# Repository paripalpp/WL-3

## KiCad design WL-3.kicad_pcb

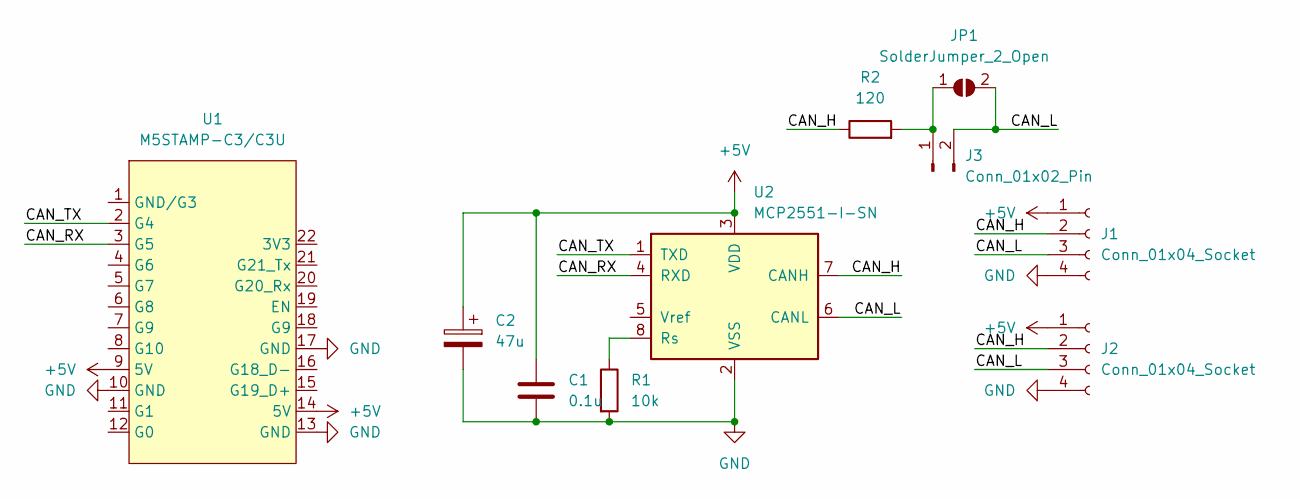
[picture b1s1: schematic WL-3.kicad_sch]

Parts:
C1: 0.1u; C_0603_1608Metric
C2: 47u; CP_Elec_6.3x7.7
J1, J2: Conn_01x04_Socket; JST_XA_S04B-XASK-1_1x04_P2.50mm_Horizontal
J3: Conn_01x02_Pin; PinHeader_1x02_P2.54mm_Vertical
JP1: SolderJumper_2_Open; SolderJumper-2_P1.3mm_Open_RoundedPad1.0x1.5mm
R1: 10k; R_0603_1608Metric
R2: 120; R_0603_1608Metric
U1: M5STAMP-C3/C3U; M5STAMP-C3C3U_SMD
U2: MCP2551-I-SN; SOIC-8_3.9x4.9mm_P1.27mm

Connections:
+5V: C1.1, C2.1, J1.1, J2.1, U1.9 (5V), U1.14 (5V), U2.3 (VDD)
/CAN_H: J1.2, J2.2, R2.1, U2.7 (CANH)
/CAN_L: J1.3, J2.3, J3.2, JP1.2 (B), U2.6 (CANL)
/CAN_RX: U1.3 (G5), U2.4 (RXD)
/CAN_TX: U1.2 (G4), U2.1 (TXD)
GND: C1.2, C2.2, J1.4, J2.4, R1.2, U1.10 (GND), U1.13 (GND), U1.17 (GND), U2.2 (VSS)
unnamed: J3.1, JP1.1 (A), R2.2
unnamed: R1.1, U2.8 (Rs)

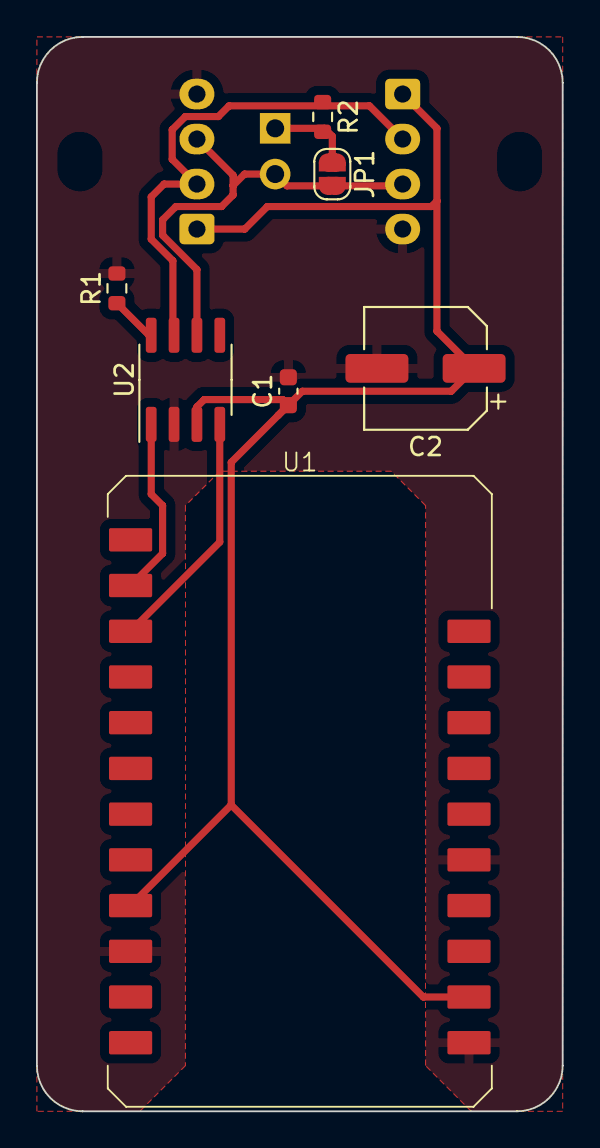
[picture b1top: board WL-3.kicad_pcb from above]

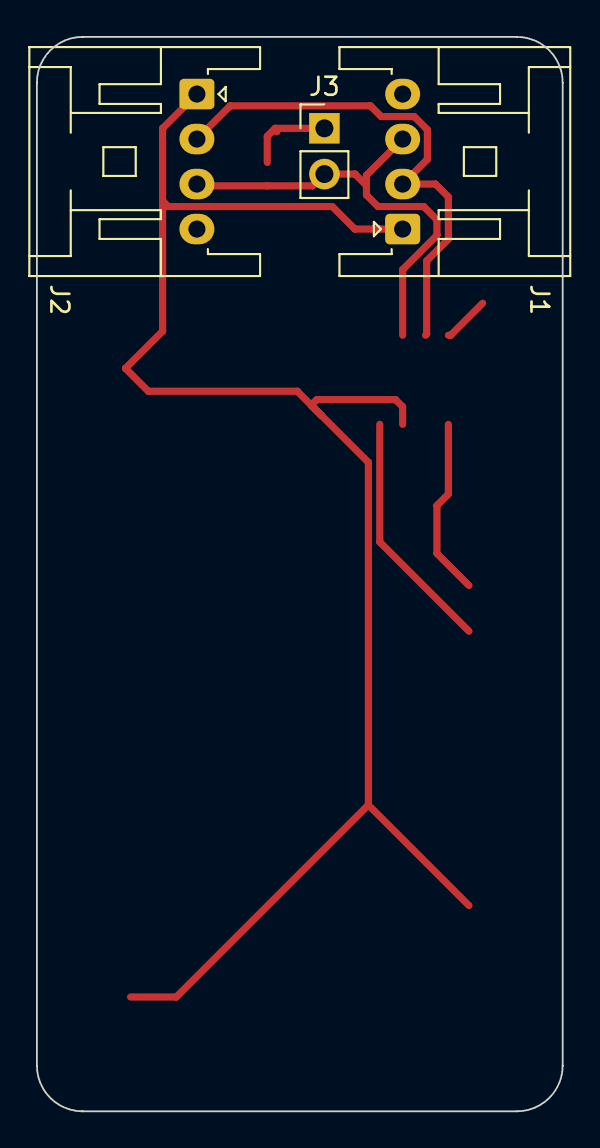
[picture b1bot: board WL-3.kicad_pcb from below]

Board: 2 copper layers, 29.2 x 59.7 mm, 10 parts (3 on the bottom side), 8 nets.
